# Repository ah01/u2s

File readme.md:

# USB To Serial Convertor Board

## Features

- Reliable (no CH340 or FTDI232RL clones) – uses [FT231SX](https://ftdichip.com/products/ft231xs/) ([datasheet](https://ftdichip.com/wp-content/uploads/2020/08/DS_FT231X.pdf))
- 3V3 logic but 5V tolerant (no switching needed)
- On board 3V3 regulator (500 mA)
- Over current protection (suitable for development)
- Connector with key (so you can make idiot-proof cables) but DuPont friendly
- Both micro and USB-C connector (they are on opposite side of the board so you cannot use both in same time, but you will have more probability to find correct cable… you know Murphys Law)

## Connector

| Pin | Dir. | Description |
|:---:|:----:| ------------|
| 1 |  | 3.3 V output (max 500 mA)¹ |
| 2 | OUT | Tx Data Enable² |
| 3 |  | GND |
| 4 |  | 5 V output (max 500 mA)¹ |
| 5 | IN | Rx |
| 6 | IN | DSR |
| 7 | OUT | Tx |
| 8 | IN | CTS |
| 9 | OUT | DTR |
| 10 | OUT | RTS |

¹ 500 mA is total maximum for 5 V  and 3.3 V output.

² Indicate transition for half-duplex communication (e.g. for RS-485).

## PCB

- [Schematics](https://raw.githubusercontent.com/ah01/u2s/master/docs/usb-to-serial.png) ([PDF](https://raw.githubusercontent.com/ah01/u2s/master/docs/usb-to-serial.pdf))
- [Sources for Eagle CAD](pcb)

<p align="center">
 &nbsp; &nbsp;

</p>

## 3D Case

There are two variants for 3D prontable case:

- [With window](3Dcase/with_holes) – connector pinout is visible via window in case)

- [Without window](3Dcase/no_holes) – connector pinout should be printed at back side as sticker

## _Erratum_ Swapped TX and RX leds (FTDI configuration template)

⚠ Labels on Tx and Rx LEDs are swapped ([explenation](ft_prog/readme.md))

This problem can be fixed in SW configuration of FT231XS. There is template for [FT Prog](https://www.ftdichip.com/Support/Utilities.htm#FT_PROG) in [ft_prog directory](ft_prog).

## Credits

- [Bastlir](https://twitter.com/bastlir) - Update of design to v2 - USB-C connector, OverCurrent LED, other minor updates based on found issues, 3D case for V2
- [OK2UQL](https://twitter.com/ok2uqlGabo) - Case for 3D printing (see [tweet for example](https://twitter.com/ok2uqlGabo/status/1366835820972376068)) (V1)

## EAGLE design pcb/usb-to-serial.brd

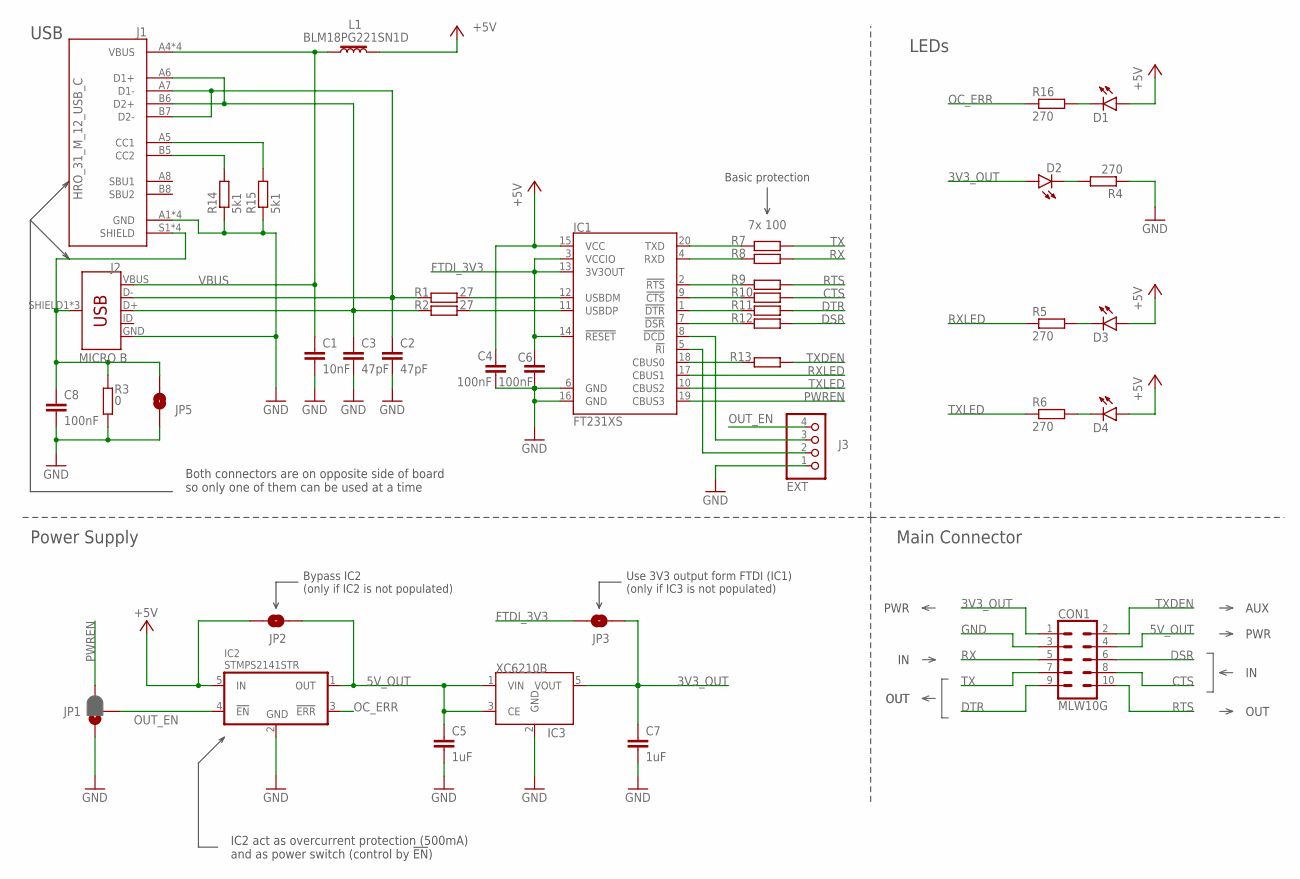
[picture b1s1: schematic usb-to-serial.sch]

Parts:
C1: 10nF; C0603
C2, C3: 47pF; C0603
C4, C6, C8: 100nF; C0603
C5, C7: 1uF; C0603
CON1: MLW10G
D1, D2, D3, D4: LEDCHIP-LED0805; CHIP-LED0805
EXT: J3; 1X04
IC1: FT231XS; SSOP20_L
IC2: STMPS2141STR; SOT23-5
IC3: XC6210B332MR; SOT-23-5
J1: HRO_31_M_12_USB_C
J2: MICRO B; USB-B-MICRO-SMD
JP1: JUMPER-SMT_3_1-NC_PASTE_NO-SILK; SMT-JUMPER_3_1-NC_PASTE_NO-SILK
JP2, JP3, JP5: JUMPER-SMT_2_NO_NO-SILK; SMT-JUMPER_2_NO_NO-SILK
L1: BLM18PG221SN1D; 0603
R1, R2: 27; R0603
R3: 0; R0603
R4, R5, R6, R16: 270; R0603
R7, R8, R9, R10, R11, R12, R13: 100; R0603
R14, R15: 5k1; R0603

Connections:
3V3_OUT: C7.1, CON1.1, D2.A, IC3.5 (VOUT), JP3.2
5V_OUT: C5.1, CON1.4, IC2.1 (OUT), IC3.1 (VIN), IC3.3 (CE), JP2.2
+5V: C4.1, D1.A, D3.A, D4.A, IC1.15 (VCC), IC2.5 (IN), JP2.1, L1.1
CTS: CON1.8, R10.2
DCD: EXT.3, IC1.8 (!DCD)
DSR: CON1.6, R12.2
DTR: CON1.9, R11.2
FTDI_3V3: C6.1, IC1.3 (VCCIO), IC1.13 (3V3OUT), IC1.14 (!RESET), JP3.1
GND: C1.2, C2.2, C3.2, C4.2, C5.2, C6.2, C7.2, C8.2, CON1.3, EXT.1, IC1.6 (GND), IC1.16 (GND), IC2.2 (GND), IC3.2 (GND), J1.A1 (GND), J1.A12 (GND), J1.B1 (GND), J1.B12 (GND), J2.GND, JP1.1, JP5.1, R3.1, R4.1, R14.1, R15.1
unnamed: IC1.18 (CBUS0), R13.1
unnamed: J1.A5 (CC1), R15.2
unnamed: IC1.20 (TXD), R7.1
unnamed: D2.C, R4.2
unnamed: J1.B5 (CC2), R14.2
unnamed: C8.1, J1.S1 (SHIELD), J1.S2 (SHIELD), J1.S3 (SHIELD), J1.S4 (SHIELD), J2.SHIELD1 (SHIELD), J2.SHIELD2 (SHIELD), J2.SHIELD3 (SHIELD), JP5.2, R3.2
unnamed: D3.C, R5.2
unnamed: D4.C, R6.2
unnamed: D1.C, R16.2
unnamed: IC1.4 (RXD), R8.1
unnamed: IC1.2 (!RTS), R9.1
unnamed: IC1.9 (!CTS), R10.1
unnamed: IC1.1 (!DTR), R11.1
unnamed: IC1.7 (!DSR), R12.1
OC_ERR: IC2.3 (!ERR), R16.1
OUT_EN: EXT.4, IC2.4 (!EN), JP1.2
PWREN: IC1.19 (CBUS3), JP1.3
RI: EXT.2, IC1.5 (!RI)
RTS: CON1.10, R9.2
RX: CON1.5, R8.2
RXLED: IC1.17 (CBUS1), R5.1
TX: CON1.7, R7.2
TXDEN: CON1.2, R13.2
TXLED: IC1.10 (CBUS2), R6.1
USBD2_N: IC1.12 (USBDM), R1.2
USBD2_P: IC1.11 (USBDP), R2.2
USBD_N: C2.1, J1.A7 (D1-), J1.B7 (D2-), J2.D-, R1.1
USBD_P: C3.1, J1.A6 (D1+), J1.B6 (D2+), J2.D+, R2.1
VBUS: C1.1, J1.A4 (VBUS), J1.A9 (VBUS), J1.B4 (VBUS), J1.B9 (VBUS), J2.VBUS, L1.2

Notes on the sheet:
USB
LEDs
Main Connector
Power Supply
Use 3V3 output form FTDI (IC1) (only if IC3 is not populated)
Both connectors are on opposite side of board so only one of them can be used at a time
7x 100
Bypass IC2 (only if IC2 is not populated)
OUT
PWR
AUX
Basic protection
IC2 act as overcurrent protection (500mA) and as power switch (control by !EN!)

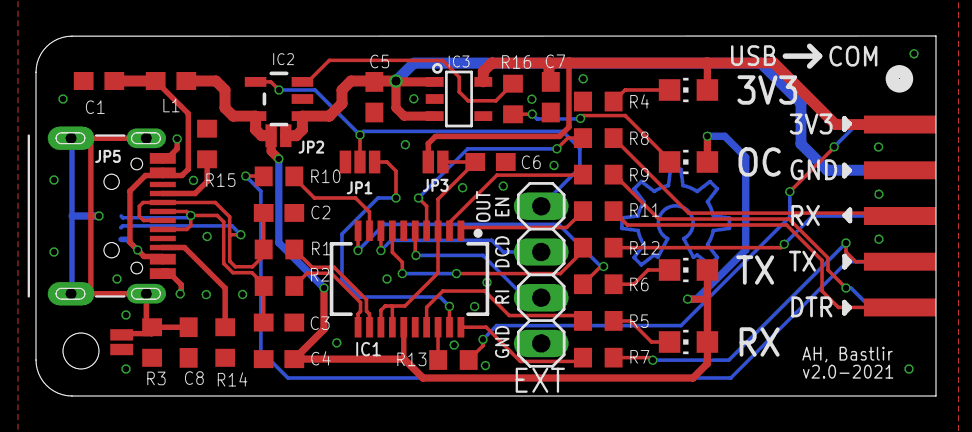
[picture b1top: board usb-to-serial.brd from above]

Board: 2 copper layers, 50.0 x 20.0 mm, 40 parts (1 on the bottom side), 38 nets.

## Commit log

2019-11-03 Source files for PCB version 1.0
2019-11-03 Template for FT configuration program
2019-11-03 Add basic readme
2019-11-29 Add github repo cover picture
2019-11-29 Add git ignore for eagle files
2019-11-29 Add ibom and rename docs
2019-11-29 Add redirect to repo root to pages home page
2019-11-29 Add link to interactive BOM
2019-11-29 Add link to iBom tool
2021-03-03 Add credits to OK2UQL (Gabo)
2021-07-05 Dev v2 merge to master (#1)
    * Update to v2
    Changes from Issues:
    - Pinout on top/bottom silkscreen
    - Add indication LED to error output of IC2 (over current shutdown)
    - Add EN pin of IC2 to EXT connector
    - Add OSHW logo to silkscreen
2021-07-10 Improve PCB image size
2021-07-10 Add info about Tx and Rx led swap + fix template
2021-07-10 Add 3D case info
2021-07-10 Update credits
2021-07-10 Fix typo

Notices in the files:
parts and their libraries:
SparkFun-Connectors: Licensing: Creative Commons ShareAlike 4.0 International - https://creativecommons.org/licenses/by-sa/4.0
